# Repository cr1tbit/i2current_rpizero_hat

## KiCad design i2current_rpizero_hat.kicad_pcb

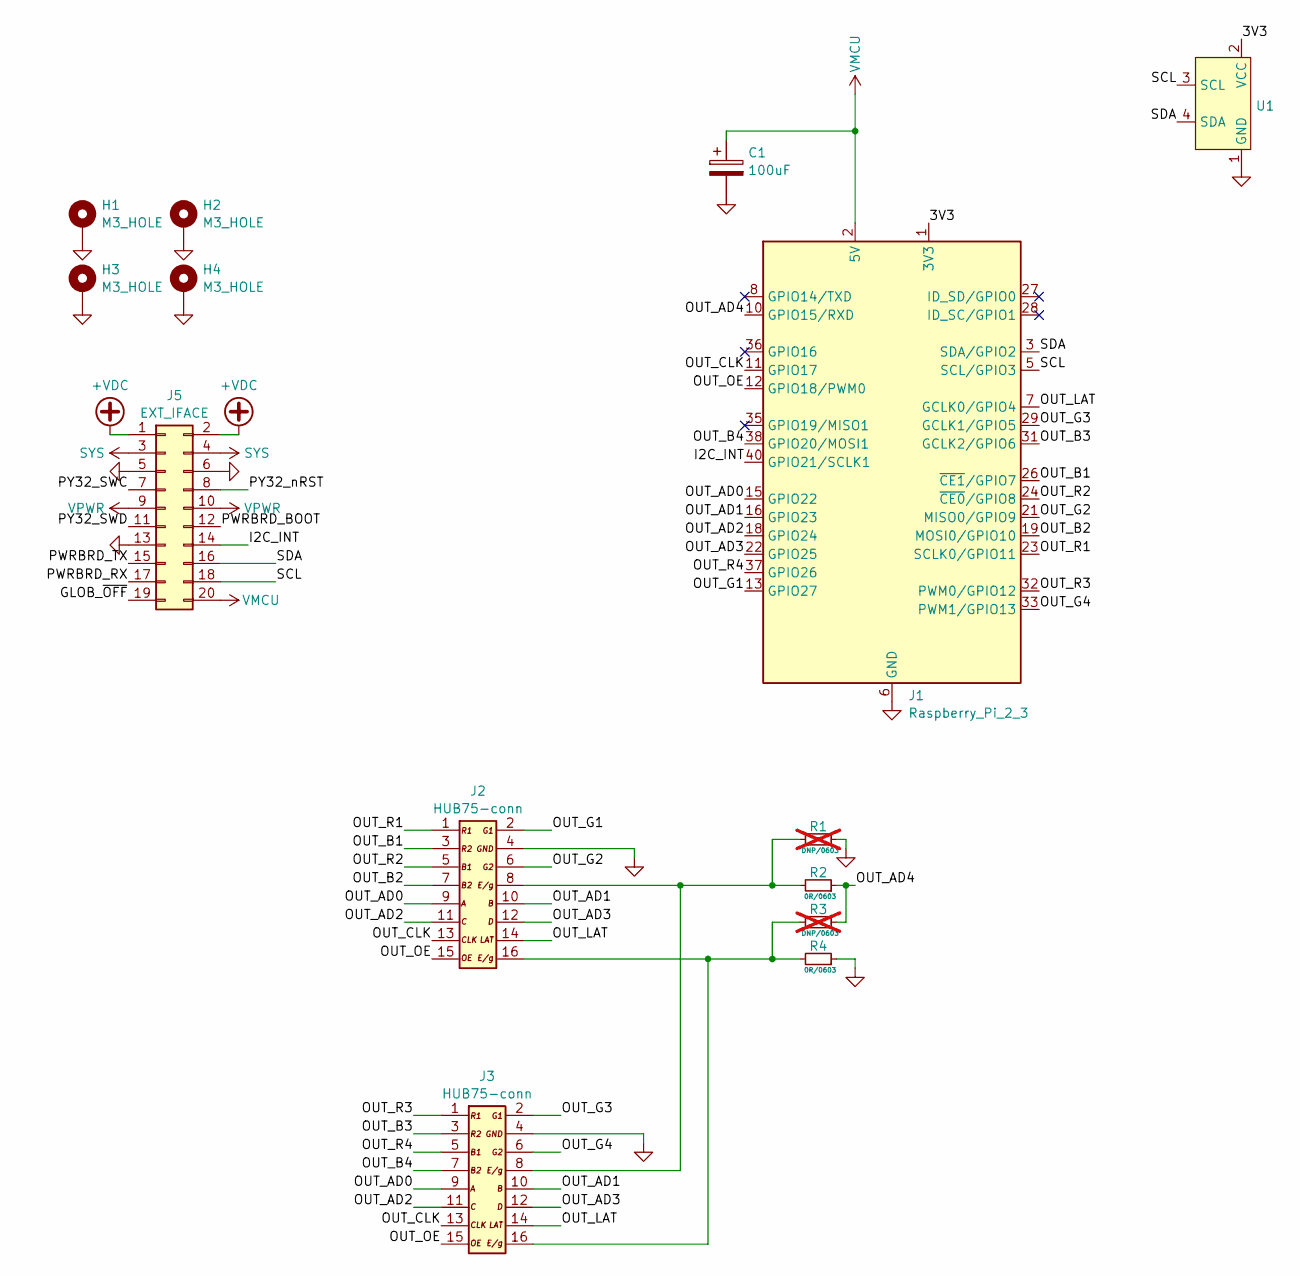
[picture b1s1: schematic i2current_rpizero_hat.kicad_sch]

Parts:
C1: 100uF; CP_Radial_D8.0mm_P5.00mm
H1, H2, H3, H4: M3_HOLE; MountingHole_3.2mm_LONGE
J1: Raspberry_Pi_2_3; Raspberry_Pi_Zero_Socketed_THT_FaceDown_MountingHoles
J2, J3: HUB75-conn; IDC-Header_2x08_P2.54mm_Vertical
J5: EXT_IFACE; PinHeader_2x10_P2.54mm_Vertical
R1, R3: DNP/0603; R_0603_1608Metric; not fitted
R2, R4: 0R/0603; R_0603_1608Metric; LCSC C21189
U1: PinHeader_1x04_P2.54mm_Vertical

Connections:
+VDC: J5.1, J5.2
/3V3: J1.1 (3V3), J1.17 (3V3), U1.2 (VCC)
/GLOB_~OFF: J5.19
/I2C_INT: J1.40 (GPIO21/SCLK1), J5.14
/OUT_AD0: J1.15 (GPIO22), J2.9, J3.9
/OUT_AD1: J1.16 (GPIO23), J2.10, J3.10
/OUT_AD2: J1.18 (GPIO24), J2.11, J3.11
/OUT_AD3: J1.22 (GPIO25), J2.12, J3.12
/OUT_AD4: J1.10 (GPIO15/RXD), R2.1, R3.1
/OUT_B1: J1.26 (~CE1/GPIO7), J2.3
/OUT_B2: J1.19 (MOSI0/GPIO10), J2.7
/OUT_B3: J1.31 (GCLK2/GPIO6), J3.3
/OUT_B4: J1.38 (GPIO20/MOSI1), J3.7
/OUT_CLK: J1.11 (GPIO17), J2.13, J3.13
/OUT_G1: J1.13 (GPIO27), J2.2
/OUT_G2: J1.21 (MISO0/GPIO9), J2.6
/OUT_G3: J1.29 (GCLK1/GPIO5), J3.2
/OUT_G4: J1.33 (PWM1/GPIO13), J3.6
/OUT_LAT: J1.7 (GCLK0/GPIO4), J2.14, J3.14
/OUT_OE: J1.12 (GPIO18/PWM0), J2.15, J3.15
/OUT_R1: J1.23 (SCLK0/GPIO11), J2.1
/OUT_R2: J1.24 (~CE0/GPIO8), J2.5
/OUT_R3: J1.32 (PWM0/GPIO12), J3.1
/OUT_R4: J1.37 (GPIO26), J3.5
/PWRBRD_BOOT: J5.12
/PWRBRD_RX: J5.17
/PWRBRD_TX: J5.15
/PY32_SWC: J5.7
/PY32_SWD: J5.11
/PY32_nRST: J5.8
/SCL: J1.5 (SCL/GPIO3), J5.18, U1.3 (SCL)
/SDA: J1.3 (SDA/GPIO2), J5.16, U1.4 (SDA)
GND: C1.2, H1.1, H2.1, H3.1, H4.1, J1.6 (GND), J1.9 (GND), J1.14 (GND), J1.20 (GND), J1.25 (GND), J1.30 (GND), J1.34 (GND), J1.39 (GND), J2.4, J3.4, J5.5, J5.6, J5.13, R1.1, R4.1, U1.1 (GND)
unnamed: J2.8, J3.8, R1.2, R2.2
unnamed: J2.16, J3.16, R3.2, R4.2
SYS: J5.3, J5.4
VMCU: C1.1, J1.2 (5V), J1.4 (5V), J5.20
VPWR: J5.9, J5.10

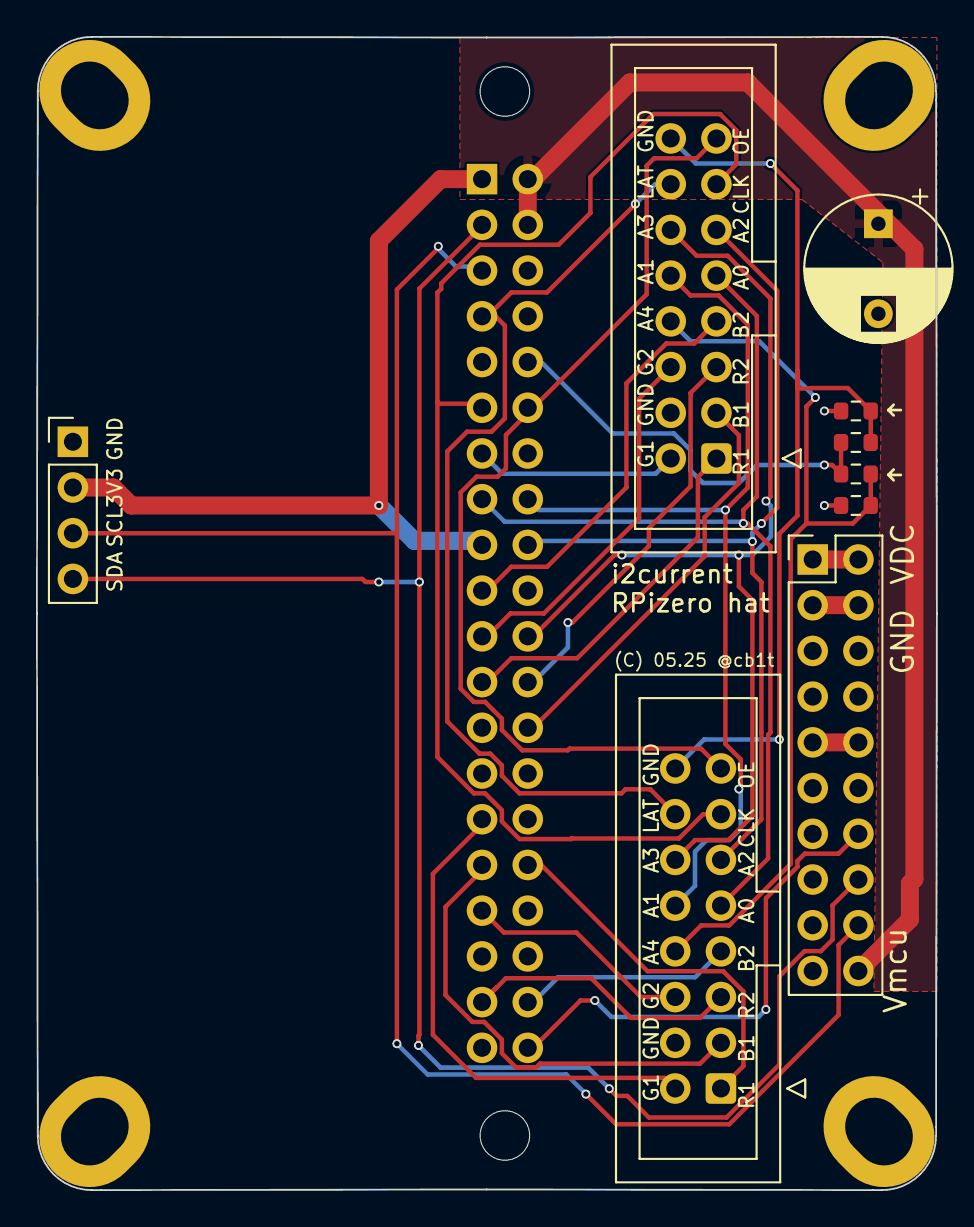
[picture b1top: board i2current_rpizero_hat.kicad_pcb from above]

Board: 2 copper layers, 50.0 x 64.1 mm, 14 parts (1 on the bottom side), 31 nets.

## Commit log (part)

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2025-04-26 Add files
